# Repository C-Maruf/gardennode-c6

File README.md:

# GardenNode-C6

A solar-powered sensor node for gardens and greenhouses. It measures soil moisture, soil temperature, air temperature and humidity, then reports everything to Home Assistant over Wi-Fi. It can also switch a 12/24 V irrigation valve or pump.

**Status:** design complete (rev A). It hasn't been fabricated, so treat it as untested hardware.

## What it does

- Runs off a single 18650 cell, charged from a small 5–9 V solar panel or USB-C
- Wakes up every 10 minutes, takes readings, sends them, and goes back to sleep
- Two capacitive soil-moisture probes, one DS18B20 soil temperature probe, and a Qwiic port for an air sensor (SHT4x, SCD4x, etc.)
- Low-side valve driver for 5–24 V solenoids, with a 30-minute safety cut-off in firmware
- Reports battery and solar voltage so you can tell whether the panel is keeping up
- Fits in a 3D-printed, gasketed enclosure with cable glands

## Repo layout

```
hw/          KiCad schematic (+ PDF)
pcb/         KiCad board, DRC report, render
fab/         Gerbers, drill files, BOM, pick-and-place, assembly drawing
enclosure/   OpenSCAD source, STL and 3MF files
firmware/    ESPHome config
tools/       Python scripts that generate and check the design
```

## Hardware

**MCU:** ESP32-C6-WROOM-1. I picked it because it has Wi-Fi 6, Bluetooth LE and an 802.15.4 radio (Zigbee/Thread) in one FCC-certified module. It also has native USB, so the board doesn't need a USB-serial chip.

**Power:**
- **Charging:** USB-C and the solar input each go through a Schottky diode into a TI BQ24074 charger.
- **Solar handling:** the charger runs in USB500 mode, so its input-voltage regulation backs the current off when the panel sags. That's a cheap stand-in for proper MPPT.
- **Charge current:** set to about 0.6 A.
- **Temperature cut-off:** an NTC next to the cell stops charging below 0 °C or above 50 °C.
- **3.3 V rail:** a TLV75733 LDO, chosen for its 25 µA quiescent current.
- **Backwards cell:** a P-channel MOSFET between the cell and the charger blocks it if the cell is inserted the wrong way round.

**Sensors:**
- **Sensor rail:** the probes are powered from a switched 3.3 V rail (P-FET on GPIO4), so they draw nothing while the node sleeps.
- **Soil probes:** each input has a 1 k / 10 nF RC filter in front of the ADC.
- **1-Wire:** the bus has a 4.7 k pull-up.

**Valve output:**
- **Switch:** a DMN3404L low-side MOSFET.
- **Protection:** a flyback diode across the valve, plus a TVS diode on the supply input.

| GPIO | Use | GPIO | Use |
|---|---|---|---|
| 0, 1 | Soil probes (ADC) | 9 | BOOT button |
| 2 | Battery voltage ÷2 | 10 | Valve |
| 3 | Solar voltage ÷4 | 11 | Status LED (active low) |
| 4 | Sensor power (low = on) | 12, 13 | USB D−/D+ |
| 5 | 1-Wire | 16, 17 | UART on J8 |
| 6, 7 | I²C SDA/SCL | 18, 19 | Charge / power-good status |
| 8 | Strapping pin, pulled up | 20–23 | Spare, on J9 |

## PCB

- 100 × 82 mm, 2 layers, 1.6 mm FR-4, 1 oz copper
- 0.2 mm minimum track/space, 0.3 mm vias, which any standard fab can build
- Power traces widened to 0.4–1.0 mm, necked down only at fine-pitch pins
- Ground pour on both sides with stitching vias
- Copper keepout on both layers under the module antenna
- No vias in component pads, except the thermal vias under the charger and the module
- All parts on the top side; every part in the BOM is stocked at Digi-Key and Mouser

DRC is clean, with no unconnected nets and no clearance errors. The few items left in `pcb/drc.rpt` are expected:
- **USB-C peg spacing:** the manufacturer's land pattern puts its alignment pegs slightly closer to the pads than my rule allows.
- **Thermal spokes:** a few single-spoke thermal reliefs.
- **Edge silkscreen:** two marks clipped at the board edge.

## Enclosure

The enclosure source is OpenSCAD, so all the dimensions are parameters at the top of the file.

**Print settings:** ASA (or PETG), 0.2 mm layers, 4 walls. The USB-C plug is printed in TPU.

**Hardware:**
- 4× M3 screws for the board
- 4× M3×12 screws for the lid
- 3× PG7 cable glands
- 2 mm silicone cord in the lid groove as a gasket
- An adhesive ePTFE vent over the small hole so it doesn't fog up inside

**Fit and mounting:** the board sits close to the USB wall so a normal USB-C cable reaches the port. Mount the box glands-down.

## Firmware

The firmware is ESPHome, in `firmware/gardennode-c6.yaml`.

1. Copy `secrets.example.yaml` to `secrets.yaml` and fill in your Wi-Fi details and an API key.
2. Build it from ESPHome Builder in Home Assistant, or run `esphome run gardennode-c6.yaml`.
3. Flash it over USB-C. If the board doesn't show up, hold BOOT and tap RESET.

**Day-to-day behaviour:**
- **Staying awake:** turn on "Stay awake" in Home Assistant when you want to update or calibrate the node. The node also stays awake while the valve is open.
- **Probe calibration:** read the raw voltage dry and in water, then set `soil_dry_v` and `soil_wet_v` to match.

## If you build one

Bring it up in this order:

1. Power it from a current-limited 5 V supply with no battery fitted. VSYS should read about 4.4 V and the 3.3 V rail 3.30 V.
2. Flash the firmware and compare the battery and solar readings against a multimeter.
3. Fit the cell and check that it charges.
4. Test a reversed cell once. The 3.3 V rail should stay at 0 V.
5. Connect a 6 V panel and check that it charges.
6. Run a 12 V valve from the valve output.
7. Measure the sleep current.

## Known limitations

- **Untested hardware:** not fabricated or tested yet.
- **No end-product FCC certification:** the module has its own modular approval, but the finished board doesn't.
- **USB charging margin:** the Schottky diode on USB costs about 0.35 V, so a weak USB supply will charge slowly.
- **Low-battery cut-out:** the LDO drops out at about 3.5 V on the cell, so usable capacity ends a little early.

## How it was made

The schematic and board are KiCad 7 files, the enclosure is OpenSCAD and the firmware is ESPHome. The netlist lives in `tools/design.py`, and the schematic, board and BOM are all generated from it. Routing was done with a custom grid router in `tools/router.py`. I developed the design.

## License

## License

MIT. See [LICENSE](LICENSE).

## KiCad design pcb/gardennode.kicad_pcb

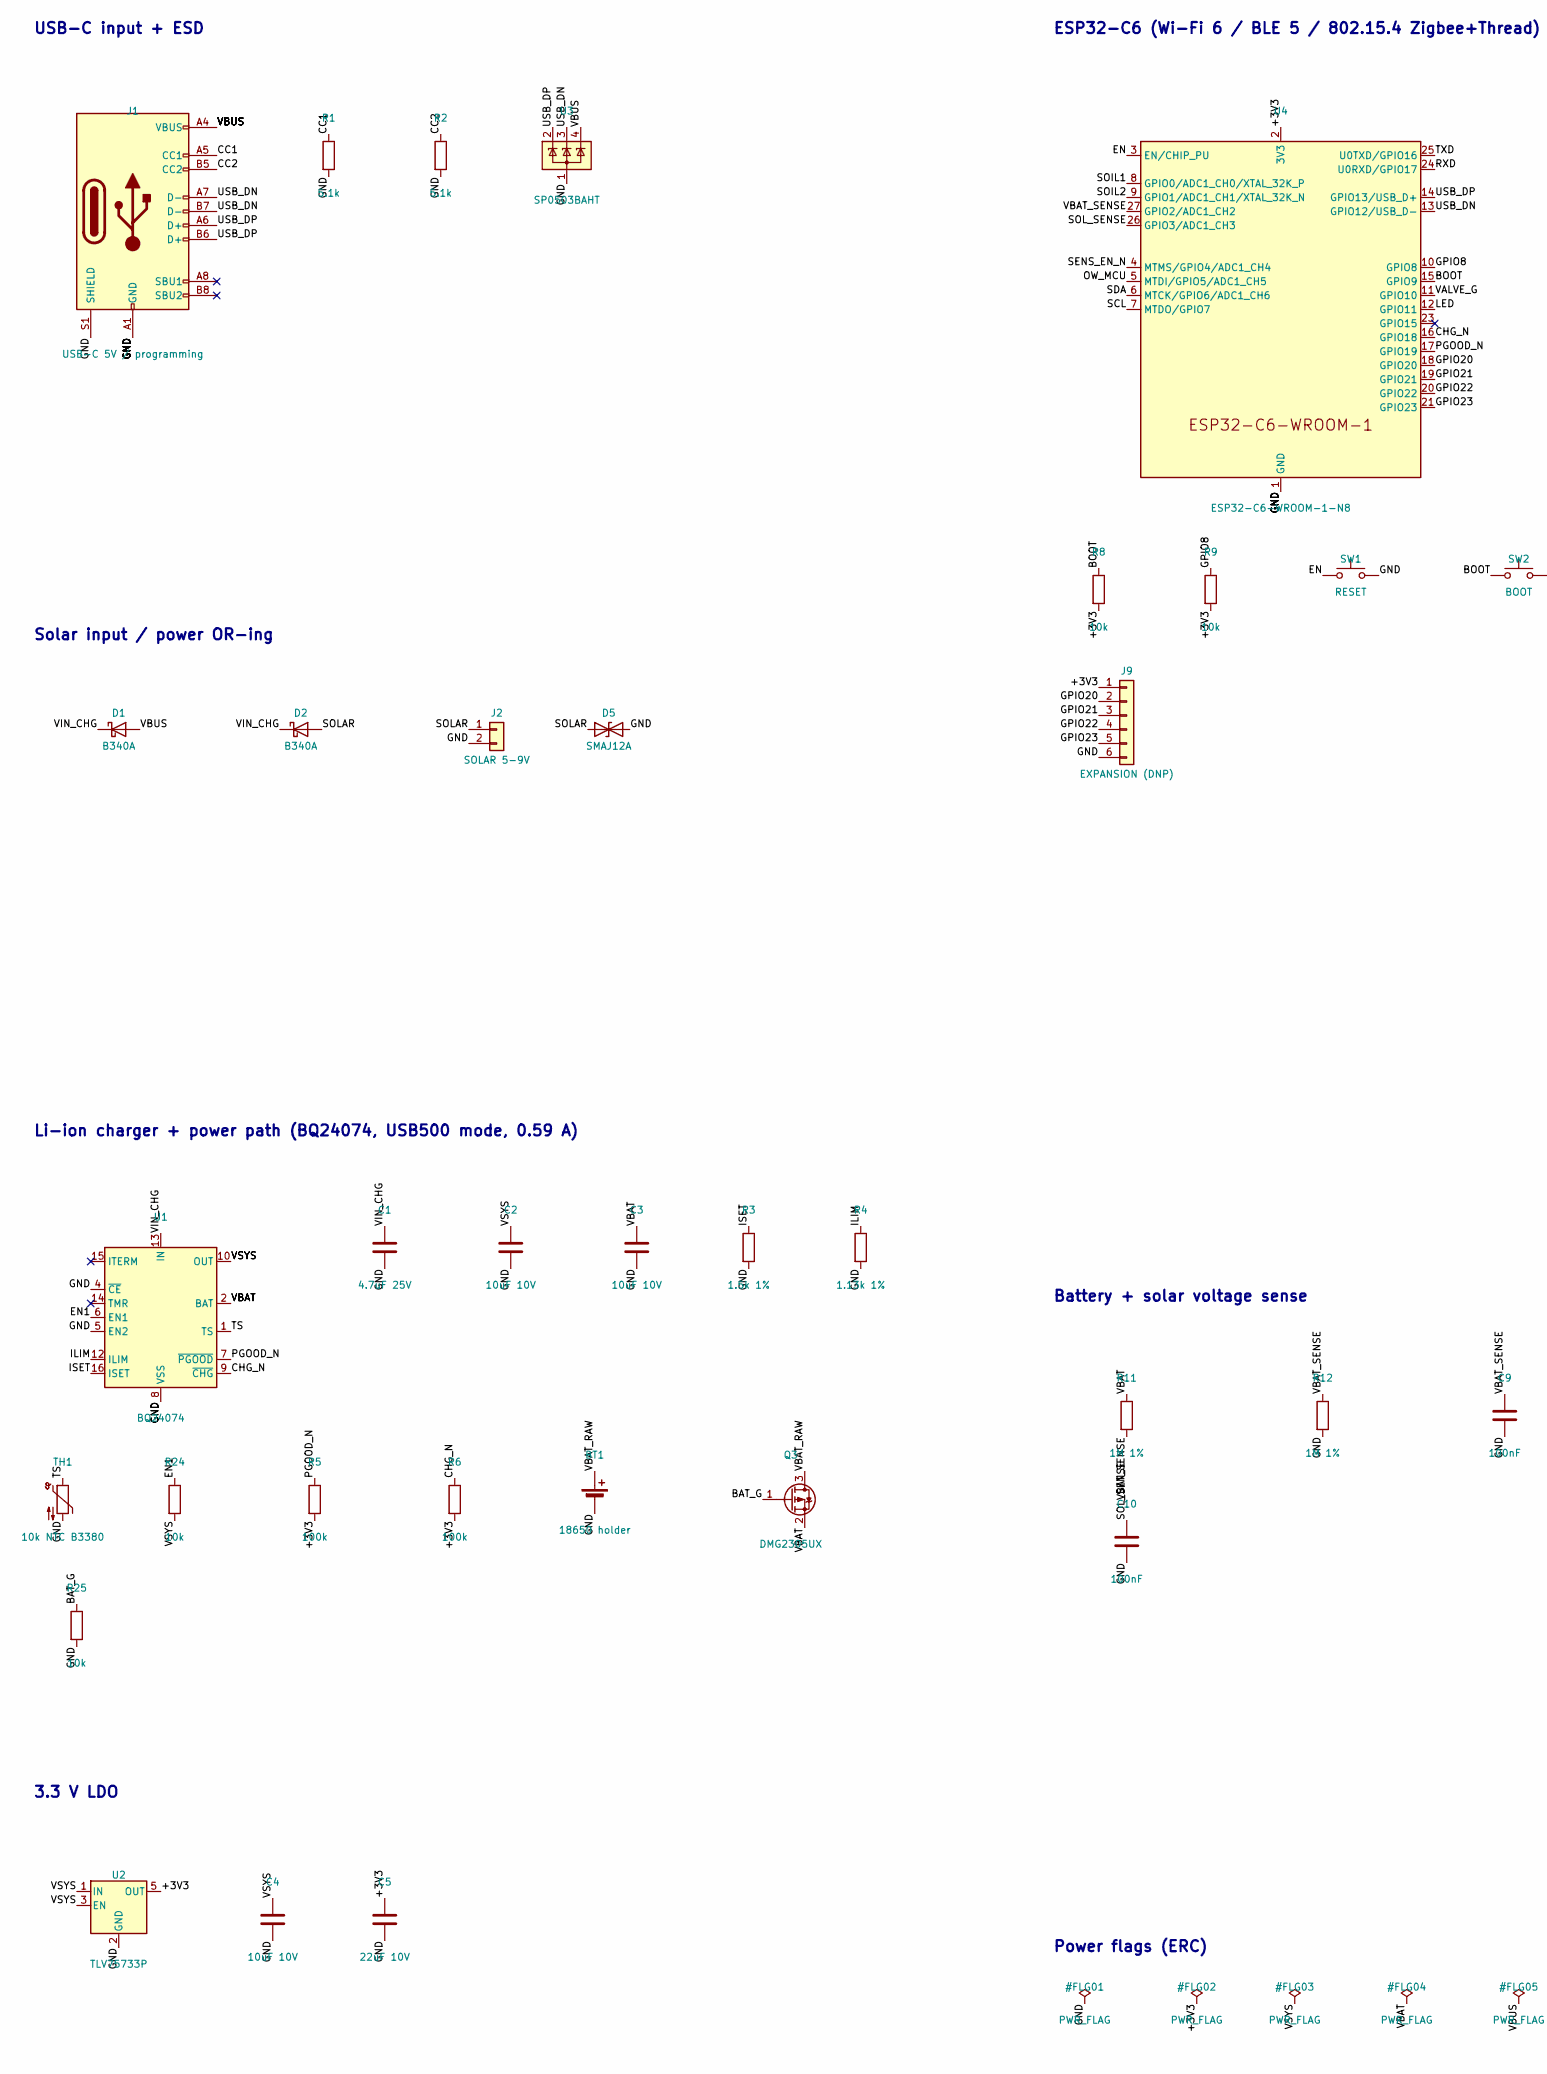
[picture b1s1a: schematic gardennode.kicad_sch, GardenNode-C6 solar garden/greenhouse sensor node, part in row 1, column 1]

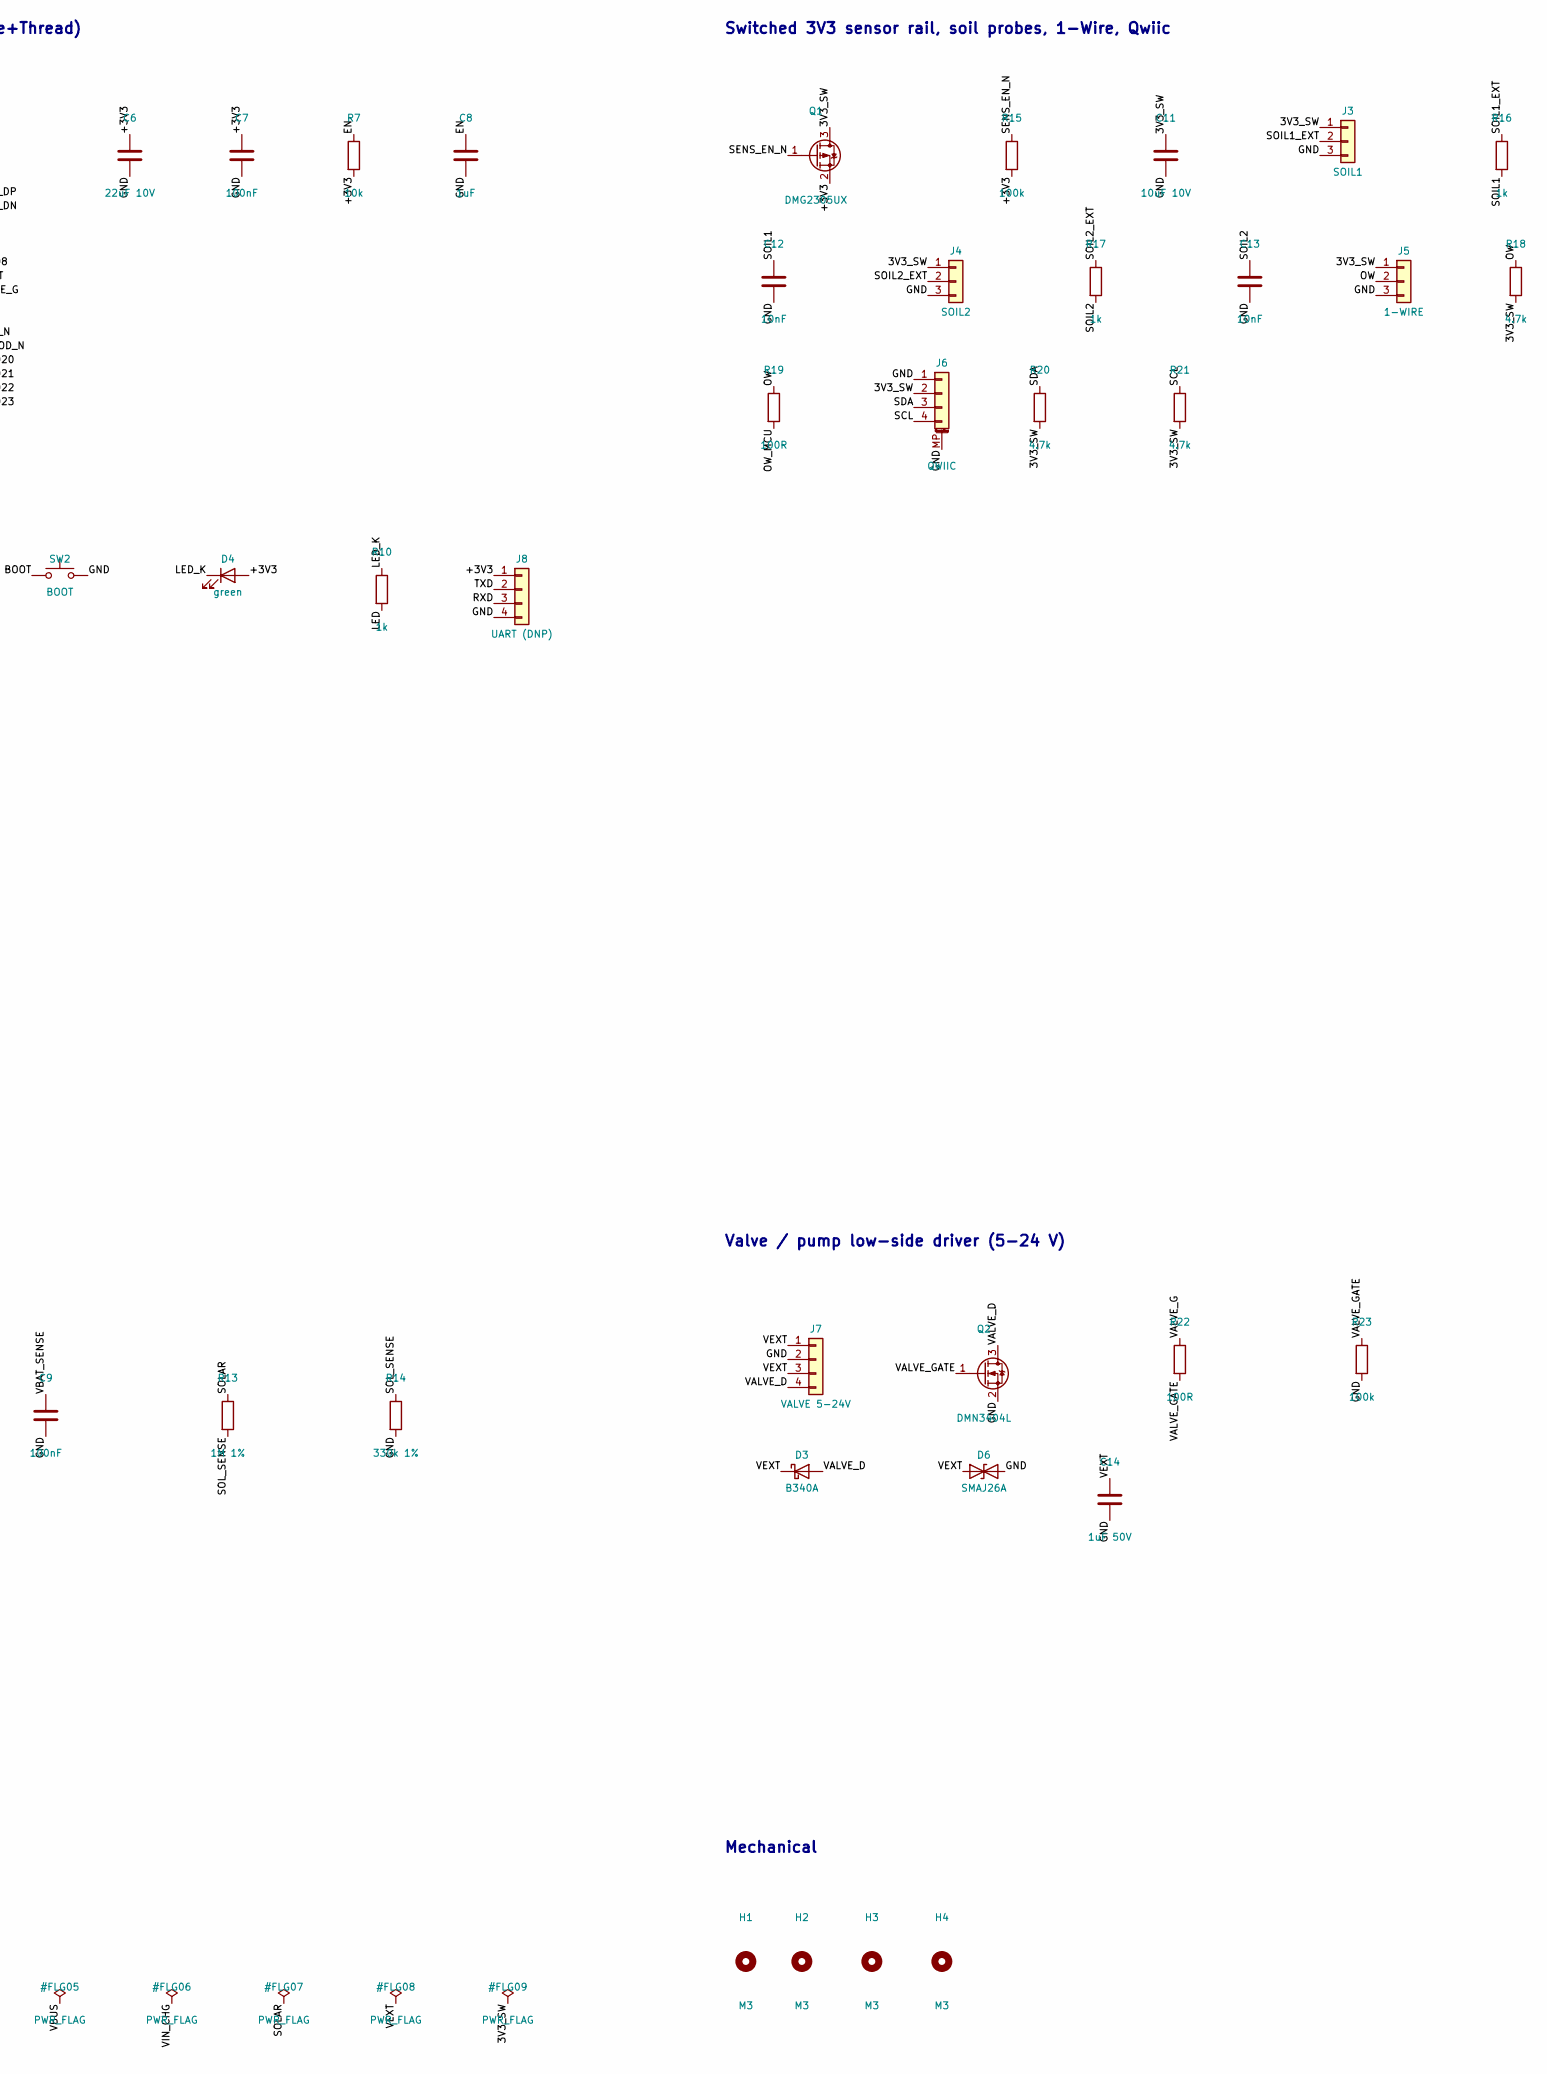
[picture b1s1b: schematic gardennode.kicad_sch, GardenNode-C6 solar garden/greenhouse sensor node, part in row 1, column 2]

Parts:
BT1: 18650 holder; BatteryHolder_Keystone_1042_1x18650; MPN 1042
C1: 4.7uF 25V; C_0805_2012Metric; MPN CL21A475KAQNNNE
C2, C3, C4, C11: 10uF 10V; C_0805_2012Metric; MPN CL21A106KPFNNNE
C5, C6: 22uF 10V; C_0805_2012Metric; MPN CL21A226MPQNNNE
C7, C9, C10: 100nF; C_0603_1608Metric; MPN CL10B104KB8NNNC
C8: 1uF; C_0603_1608Metric; MPN CL10A105KB8NNNC
C12, C13: 10nF; C_0603_1608Metric; MPN CL10B103KB8NNNC
C14: 1uF 50V; C_0805_2012Metric; MPN CL21B105KBFNNNE
D1, D2, D3: B340A; D_SMA; MPN B340A-13-F
D4: green; LED_0603_1608Metric; MPN LTST-C191KGKT
D5: SMAJ12A; D_SMA; MPN SMAJ12A
D6: SMAJ26A; D_SMA; MPN SMAJ26A
H1, H2, H3, H4: M3; MountingHole_3.2mm_M3
J1: USB-C 5V / programming; USB_C_Receptacle_GCT_USB4105-xx-A_16P_TopMnt_Horizontal; MPN USB4105-GF-A
J2: SOLAR 5-9V; TerminalBlock_Phoenix_PT-1,5-2-3.5-H_1x02_P3.50mm_Horizontal; MPN 1984617
J3: SOIL1; JST_PH_B3B-PH-K_1x03_P2.00mm_Vertical; MPN B3B-PH-K-S(LF)(SN)
J4: SOIL2; JST_PH_B3B-PH-K_1x03_P2.00mm_Vertical; MPN B3B-PH-K-S(LF)(SN)
J5: 1-WIRE; JST_PH_B3B-PH-K_1x03_P2.00mm_Vertical; MPN B3B-PH-K-S(LF)(SN)
J6: QWIIC; JST_SH_SM04B-SRSS-TB_1x04-1MP_P1.00mm_Horizontal; MPN SM04B-SRSS-TB(LF)(SN)
J7: VALVE 5-24V; TerminalBlock_Phoenix_PT-1,5-4-3.5-H_1x04_P3.50mm_Horizontal; MPN 1984633
J8: UART (DNP); PinHeader_1x04_P2.54mm_Vertical; MPN DNP
J9: EXPANSION (DNP); PinHeader_1x06_P2.54mm_Vertical; MPN DNP
Q1, Q3: DMG2305UX; SOT-23; MPN DMG2305UX-7
Q2: DMN3404L; SOT-23; MPN DMN3404L-7
R1, R2: 5.1k; R_0603_1608Metric; MPN RC0603FR-075K1L
R3: 1.5k 1%; R_0603_1608Metric; MPN RC0603FR-071K5L
R4: 1.13k 1%; R_0603_1608Metric; MPN RC0603FR-071K13L
R5, R6, R15, R23: 100k; R_0603_1608Metric; MPN RC0603FR-07100KL
R7, R8, R9, R24, R25: 10k; R_0603_1608Metric; MPN RC0603FR-0710KL
R10, R16, R17: 1k; R_0603_1608Metric; MPN RC0603FR-071KL
R11, R12, R13: 1M 1%; R_0603_1608Metric; MPN RC0603FR-071ML
R14: 330k 1%; R_0603_1608Metric; MPN RC0603FR-07330KL
R18, R20, R21: 4.7k; R_0603_1608Metric; MPN RC0603FR-074K7L
R19, R22: 100R; R_0603_1608Metric; MPN RC0603FR-07100RL
SW1: RESET; SW_Push_1P1T_NO_CK_KMR2; MPN KMR221GLFS
SW2: BOOT; SW_Push_1P1T_NO_CK_KMR2; MPN KMR221GLFS
TH1: 10k NTC B3380; R_0603_1608Metric; MPN NCP18XH103F03RB
U1: BQ24074; VQFN-16-1EP_3x3mm_P0.5mm_EP1.6x1.6mm; MPN BQ24074RGTR
U2: TLV75733P; SOT-23-5; MPN TLV75733PDBVR
U3: SP0503BAHT; SOT-143; MPN SP0503BAHTG
U4: ESP32-C6-WROOM-1-N8; ESP32-C6-WROOM-1; MPN ESP32-C6-WROOM-1-N8

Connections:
3V3_SW: C11.1, J3.1, J4.1, J5.1, J6.2, Q1.3 (D), R18.2, R20.2, R21.2
+3V3: C5.1, C6.1, C7.1, D4.2 (A), J8.1, J9.1, Q1.2 (S), R5.2, R6.2, R7.2, R8.2, R9.2, R15.2, U2.5 (OUT), U4.2 (3V3)
BAT_G: Q3.1 (G), R25.1
BOOT: R8.1, SW2.1, U4.15 (GPIO9)
CC1: J1.A5 (CC1), R1.1
CC2: J1.B5 (CC2), R2.1
CHG_N: R6.1, U1.9 (~CHG), U4.16 (GPIO18)
EN: C8.1, R7.1, SW1.1, U4.3 (EN/CHIP_PU)
EN1: R24.1, U1.6 (EN1)
GND: BT1.2 (-), C1.2, C2.2, C3.2, C4.2, C5.2, C6.2, C7.2, C8.2, C9.2, C10.2, C11.2, C12.2, C13.2, C14.2, D5.2 (A2), D6.2 (A2), J1.A1 (GND), J1.A12 (GND), J1.B1 (GND), J1.B12 (GND), J1.S1 (SHIELD), J2.2, J3.3, J4.3, J5.3, J6.1, J6.MP (MountPin), J7.2, J8.4, J9.6, Q2.2 (S), R1.2, R2.2, R3.2, R4.2, R12.2, R14.2, R23.2, R25.2, SW1.2, SW2.2, TH1.2, U1.4 (~CE), U1.5 (EN2), U1.8 (VSS), U1.17 (VSS), U2.2 (GND), U3.1 (A), U4.1 (GND), U4.28 (GND), U4.29 (GND)
GPIO8: R9.1, U4.10 (GPIO8)
GPIO20: J9.2, U4.18 (GPIO20)
GPIO21: J9.3, U4.19 (GPIO21)
GPIO22: J9.4, U4.20 (GPIO22)
GPIO23: J9.5, U4.21 (GPIO23)
ILIM: R4.1, U1.12 (ILIM)
ISET: R3.1, U1.16 (ISET)
LED: R10.2, U4.12 (GPIO11)
LED_K: D4.1 (K), R10.1
OW: J5.2, R18.1, R19.1
OW_MCU: R19.2, U4.5 (MTDI/GPIO5/ADC1_CH5)
PGOOD_N: R5.1, U1.7 (~PGOOD), U4.17 (GPIO19)
RXD: J8.3, U4.24 (U0RXD/GPIO17)
SCL: J6.4, R21.1, U4.7 (MTDO/GPIO7)
SDA: J6.3, R20.1, U4.6 (MTCK/GPIO6/ADC1_CH6)
SENS_EN_N: Q1.1 (G), R15.1, U4.4 (MTMS/GPIO4/ADC1_CH4)
SOIL1: C12.1, R16.2, U4.8 (GPIO0/ADC1_CH0/XTAL_32K_P)
SOIL1_EXT: J3.2, R16.1
SOIL2: C13.1, R17.2, U4.9 (GPIO1/ADC1_CH1/XTAL_32K_N)
SOIL2_EXT: J4.2, R17.1
SOLAR: D2.2 (A), D5.1 (A1), J2.1, R13.1
SOL_SENSE: C10.1, R13.2, R14.1, U4.26 (GPIO3/ADC1_CH3)
TS: TH1.1, U1.1 (TS)
TXD: J8.2, U4.25 (U0TXD/GPIO16)
USB_DN: J1.A7 (D-), J1.B7 (D-), U3.3 (K), U4.13 (GPIO12/USB_D-)
USB_DP: J1.A6 (D+), J1.B6 (D+), U3.2 (K), U4.14 (GPIO13/USB_D+)
VALVE_D: D3.2 (A), J7.4, Q2.3 (D)
VALVE_G: R22.1, U4.11 (GPIO10)
VALVE_GATE: Q2.1 (G), R22.2, R23.1
VBAT: C3.1, Q3.2 (S), R11.1, U1.2 (BAT), U1.3 (BAT)
VBAT_RAW: BT1.1 (+), Q3.3 (D)
VBAT_SENSE: C9.1, R11.2, R12.1, U4.27 (GPIO2/ADC1_CH2)
VBUS: D1.2 (A), J1.A4 (VBUS), J1.A9 (VBUS), J1.B4 (VBUS), J1.B9 (VBUS), U3.4 (K)
VEXT: C14.1, D3.1 (K), D6.1 (A1), J7.1, J7.3
VIN_CHG: C1.1, D1.1 (K), D2.1 (K), U1.13 (IN)
VSYS: C2.1, C4.1, R24.2, U1.10 (OUT), U1.11 (OUT), U2.1 (IN), U2.3 (EN)

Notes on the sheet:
USB-C input + ESD
Solar input / power OR-ing
Li-ion charger + power path (BQ24074, USB500 mode, 0.59 A)
3.3 V LDO
ESP32-C6 (Wi-Fi 6 / BLE 5 / 802.15.4 Zigbee+Thread)
Battery + solar voltage sense
Switched 3V3 sensor rail, soil probes, 1-Wire, Qwiic
Valve / pump low-side driver (5-24 V)
Mechanical
Power flags (ERC)

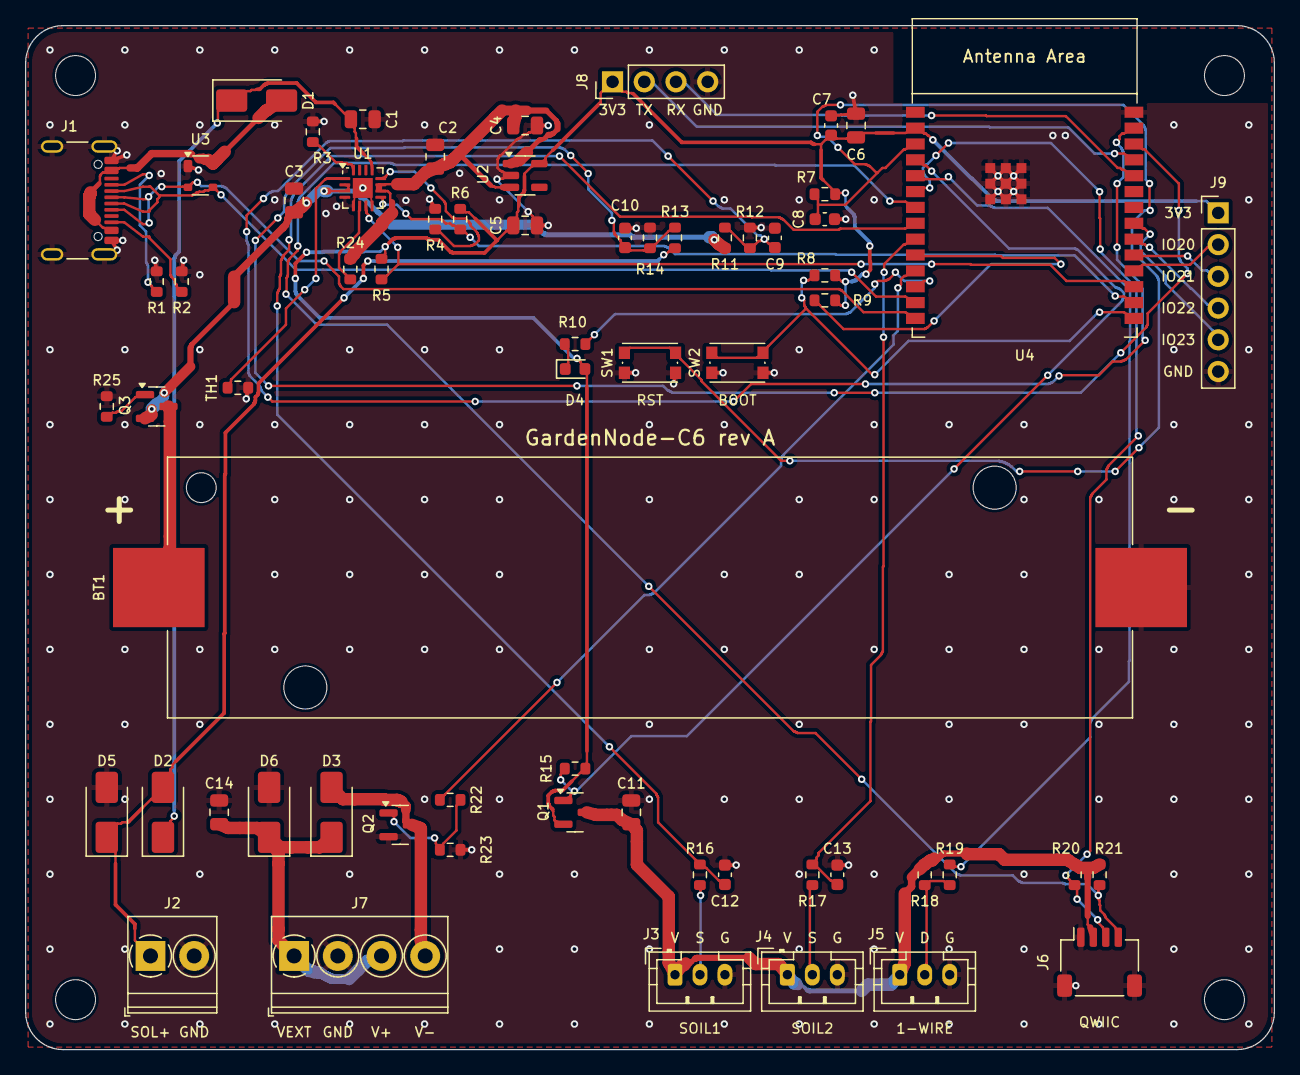
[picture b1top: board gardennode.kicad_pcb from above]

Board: 2 copper layers, 100.0 x 82.0 mm, 69 parts (0 on the bottom side), 46 nets.

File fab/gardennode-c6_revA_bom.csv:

Item,Qty,References,Value,Footprint,Manufacturer,MPN,US distributors,Approved alternate,Populate
1,1,BT1,18650 holder,BatteryHolder_Keystone_1042_1x18650,Keystone,1042,"DK, MO",1042P (polarized),Yes
2,1,C1,4.7uF 25V,C_0805_2012Metric,Samsung Electro-Mechanics,CL21A475KAQNNNE,"DK, MO","any AEC/X7R-equivalent 0603/0805 part, same value/voltage/tolerance",Yes
3,4,C2 C3 C4 C11,10uF 10V,C_0805_2012Metric,Samsung Electro-Mechanics,CL21A106KPFNNNE,"DK, MO","any AEC/X7R-equivalent 0603/0805 part, same value/voltage/tolerance",Yes
4,2,C5 C6,22uF 10V,C_0805_2012Metric,Samsung Electro-Mechanics,CL21A226MPQNNNE,"DK, MO","any AEC/X7R-equivalent 0603/0805 part, same value/voltage/tolerance",Yes
5,3,C7 C9 C10,100nF,C_0603_1608Metric,Samsung Electro-Mechanics,CL10B104KB8NNNC,"DK, MO","any AEC/X7R-equivalent 0603/0805 part, same value/voltage/tolerance",Yes
6,1,C8,1uF,C_0603_1608Metric,Samsung Electro-Mechanics,CL10A105KB8NNNC,"DK, MO","any AEC/X7R-equivalent 0603/0805 part, same value/voltage/tolerance",Yes
7,2,C12 C13,10nF,C_0603_1608Metric,Samsung Electro-Mechanics,CL10B103KB8NNNC,"DK, MO","any AEC/X7R-equivalent 0603/0805 part, same value/voltage/tolerance",Yes
8,1,C14,1uF 50V,C_0805_2012Metric,Samsung Electro-Mechanics,CL21B105KBFNNNE,"DK, MO","any AEC/X7R-equivalent 0603/0805 part, same value/voltage/tolerance",Yes
9,3,D1 D2 D3,B340A,D_SMA,Diodes Inc,B340A-13-F,"DK, MO",B340A-E3/61T (Vishay),Yes
10,1,D4,green,LED_0603_1608Metric,Lite-On,LTST-C191KGKT,"DK, MO",,Yes
11,1,D5,SMAJ12A,D_SMA,Littelfuse,SMAJ12A,"DK, MO",SMAJ12A-13-F (Diodes),Yes
12,1,D6,SMAJ26A,D_SMA,Littelfuse,SMAJ26A,"DK, MO",SMAJ26A-13-F (Diodes),Yes
13,1,J1,USB-C 5V / programming,USB_C_Receptacle_GCT_USB4105-xx-A_16P_TopMnt_Horizontal,GCT,USB4105-GF-A,"DK, MO",USB4105-GF-A-060,Yes
14,1,J2,SOLAR 5-9V,"TerminalBlock_Phoenix_PT-1,5-2-3.5-H_1x02_P3.50mm_Horizontal",Phoenix Contact,1984617,"DK, MO",,Yes
15,1,J3,SOIL1,JST_PH_B3B-PH-K_1x03_P2.00mm_Vertical,JST,B3B-PH-K-S(LF)(SN),"DK, MO",,Yes
16,1,J4,SOIL2,JST_PH_B3B-PH-K_1x03_P2.00mm_Vertical,JST,B3B-PH-K-S(LF)(SN),"DK, MO",,Yes
17,1,J5,1-WIRE,JST_PH_B3B-PH-K_1x03_P2.00mm_Vertical,JST,B3B-PH-K-S(LF)(SN),"DK, MO",,Yes
18,1,J6,QWIIC,JST_SH_SM04B-SRSS-TB_1x04-1MP_P1.00mm_Horizontal,JST,SM04B-SRSS-TB(LF)(SN),"DK, MO",,Yes
19,1,J7,VALVE 5-24V,"TerminalBlock_Phoenix_PT-1,5-4-3.5-H_1x04_P3.50mm_Horizontal",Phoenix Contact,1984633,"DK, MO",,Yes
20,1,J8,UART (DNP),PinHeader_1x04_P2.54mm_Vertical,-,"PRT-00116 (SparkFun) or any 0.1"" header",-,,DNP
21,1,J9,EXPANSION (DNP),PinHeader_1x06_P2.54mm_Vertical,-,"PRT-00116 (SparkFun) or any 0.1"" header",-,,DNP
22,2,Q1 Q3,DMG2305UX,SOT-23,Diodes Inc,DMG2305UX-7,"DK, MO",DMG2307L-7,Yes
23,1,Q2,DMN3404L,SOT-23,Diodes Inc,DMN3404L-7,"DK, MO",DMG3404L-7,Yes
24,2,R1 R2,5.1k,R_0603_1608Metric,Yageo,RC0603FR-075K1L,"DK, MO","any AEC/X7R-equivalent 0603/0805 part, same value/voltage/tolerance",Yes
25,1,R3,1.5k 1%,R_0603_1608Metric,Yageo,RC0603FR-071K5L,"DK, MO","any AEC/X7R-equivalent 0603/0805 part, same value/voltage/tolerance",Yes
26,1,R4,1.13k 1%,R_0603_1608Metric,Yageo,RC0603FR-071K13L,"DK, MO","any AEC/X7R-equivalent 0603/0805 part, same value/voltage/tolerance",Yes
27,4,R5 R6 R15 R23,100k,R_0603_1608Metric,Yageo,RC0603FR-07100KL,"DK, MO","any AEC/X7R-equivalent 0603/0805 part, same value/voltage/tolerance",Yes
28,5,R7 R8 R9 R24 R25,10k,R_0603_1608Metric,Yageo,RC0603FR-0710KL,"DK, MO","any AEC/X7R-equivalent 0603/0805 part, same value/voltage/tolerance",Yes
29,3,R10 R16 R17,1k,R_0603_1608Metric,Yageo,RC0603FR-071KL,"DK, MO","any AEC/X7R-equivalent 0603/0805 part, same value/voltage/tolerance",Yes
30,3,R11 R12 R13,1M 1%,R_0603_1608Metric,Yageo,RC0603FR-071ML,"DK, MO","any AEC/X7R-equivalent 0603/0805 part, same value/voltage/tolerance",Yes
31,1,R14,330k 1%,R_0603_1608Metric,Yageo,RC0603FR-07330KL,"DK, MO","any AEC/X7R-equivalent 0603/0805 part, same value/voltage/tolerance",Yes
32,3,R18 R20 R21,4.7k,R_0603_1608Metric,Yageo,RC0603FR-074K7L,"DK, MO","any AEC/X7R-equivalent 0603/0805 part, same value/voltage/tolerance",Yes
33,2,R19 R22,100R,R_0603_1608Metric,Yageo,RC0603FR-07100RL,"DK, MO","any AEC/X7R-equivalent 0603/0805 part, same value/voltage/tolerance",Yes
34,1,SW1,RESET,SW_Push_1P1T_NO_CK_KMR2,C&K,KMR221GLFS,"DK, MO",,Yes
35,1,SW2,BOOT,SW_Push_1P1T_NO_CK_KMR2,C&K,KMR221GLFS,"DK, MO",,Yes
36,1,TH1,10k NTC B3380,R_0603_1608Metric,Murata,NCP18XH103F03RB,"DK, MO",NTCG163JF103FT1 (TDK),Yes
37,1,U1,BQ24074,VQFN-16-1EP_3x3mm_P0.5mm_EP1.6x1.6mm,Texas Instruments,BQ24074RGTR,"DK, MO, TI.com",BQ24074RGTT (small reel),Yes
38,1,U2,TLV75733P,SOT-23-5,Texas Instruments,TLV75733PDBVR,"DK, MO, TI.com","TLV75733PDYDR, TLV75533PDBVR (0.5 A)",Yes
39,1,U3,SP0503BAHT,SOT-143,Littelfuse,SP0503BAHTG,"DK, MO",,Yes
40,1,U4,ESP32-C6-WROOM-1-N8,ESP32-C6-WROOM-1,Espressif,ESP32-C6-WROOM-1-N8,"DK, MO",ESP32-C6-WROOM-1-N4 (4 MB flash),Yes

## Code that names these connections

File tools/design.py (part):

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P(R('R2', '5.1k', 'CC2', 'GND', 'RC0603FR-075K1L', grp='usb'))
P(dict(ref='U3', lib=SYM+'Power_Protection.kicad_sym', sym='SP0503BAHT', fp='Package_TO_SOT_SMD:SOT-143',
       value='SP0503BAHT', mfr='Littelfuse', mpn='SP0503BAHTG',
       pins={'1': 'GND', '2': 'USB_DP', '3': 'USB_DN', '4': 'VBUS'}, grp='usb'))

# ---------------- Power input OR-ing ----------------
P(dict(ref='D1', lib=SYM+'Device.kicad_sym', sym='D_Schottky', fp='Diode_SMD:D_SMA', value='B340A',
       mfr='Diodes Inc', mpn='B340A-13-F', pins={'1': 'VIN_CHG', '2': 'VBUS'}, grp='pwr'))
P(dict(ref='D2', lib=SYM+'Device.kicad_sym', sym='D_Schottky', fp='Diode_SMD:D_SMA', value='B340A',
       mfr='Diodes Inc', mpn='B340A-13-F', pins={'1': 'VIN_CHG', '2': 'SOLAR'}, grp='pwr'))
P(dict(ref='J2', lib=SYM+'Connector_Generic.kicad_sym', sym='Conn_01x02',
       fp='TerminalBlock_Phoenix:TerminalBlock_Phoenix_PT-1,5-2-3.5-H_1x02_P3.50mm_Horizontal',
       value='SOLAR 5-9V', mfr='Phoenix Contact', mpn='1984617', pins={'1': 'SOLAR', '2': 'GND'}, grp='pwr'))
P(dict(ref='D5', lib=SYM+'Device.kicad_sym', sym='D_TVS', fp='Diode_SMD:D_SMA', value='SMAJ12A',
       mfr='Littelfuse', mpn='SMAJ12A', pins={'1': 'SOLAR', '2': 'GND'}, grp='pwr'))

# ---------------- Charger BQ24074 ----------------
P(dict(ref='U1', lib=SYM+'Battery_Management.kicad_sym', sym='BQ24074RGT',
       fp='Package_DFN_QFN:VQFN-16-1EP_3x3mm_P0.5mm_EP1.6x1.6mm', value='BQ24074', mfr='Texas Instruments', mpn='BQ24074RGTR',
       pins={'1': 'TS', '2': 'VBAT', '3': 'VBAT', '4': 'GND', '5': 'GND', '6': 'EN1', '7': 'PGOOD_N', '8': 'GND',
             '9': 'CHG_N', '10': 'VSYS', '11': 'VSYS', '12': 'ILIM', '13': 'VIN_CHG', '14': NC, '15': NC, '16': 'ISET', '17': 'GND'}, grp='chg'))
P(C('C1', '4.7uF 25V', 'VIN_CHG', 'GND', 'CL21A475KAQNNNE', fp='Capacitor_SMD:C_0805_2012Metric', grp='chg'))
P(C('C2', '10uF 10V', 'VSYS', 'GND', 'CL21A106KPFNNNE', fp='Capacitor_SMD:C_0805_2012Metric', grp='chg'))
P(C('C3', '10uF 10V', 'VBAT', 'GND', 'CL21A106KPFNNNE', fp='Capacitor_SMD:C_0805_2012Metric', grp='chg'))
P(R('R3', '1.5k 1%', 'ISET', 'GND', 'RC0603FR-071K5L', grp='chg'))      # ICHG = 890/1500 = 0.59 A
P(R('R4', '1.13k 1%', 'ILIM', 'GND', 'RC0603FR-071K13L', grp='chg'))    # only used if EN2=1/EN1=0
P(dict(ref='TH1', lib=SYM+'Device.kicad_sym', sym='Thermistor_NTC', fp='Resistor_SMD:R_0603_1608Metric',
       value='10k NTC B3380', mfr='Murata', mpn='NCP18XH103F03RB', pins={'1': 'TS', '2': 'GND'}, grp='chg'))
P(R('R24', '10k', 'EN1', 'VSYS', 'RC0603FR-0710KL', grp='chg'))   # EN1=1, EN2=0 -> USB500 (VIN-DPM active)
P(R('R5', '100k', 'PGOOD_N', '+3V3', 'RC0603FR-07100KL', grp='chg'))
P(R('R6', '100k', 'CHG_N', '+3V3', 'RC0603FR-07100KL', grp='chg'))
P(dict(ref='BT1', lib=SYM+'Device.kicad_sym', sym='Battery_Cell', fp='Battery:BatteryHolder_Keystone_1042_1x18650',
       value='18650 holder', mfr='Keystone', mpn='1042', pins={'1': 'VBAT_RAW', '2': 'GND'}, grp='chg'))
# reverse-battery protection: P-FET, drain to cell +, source to VBAT, gate to GND.
# Correct cell: body diode conducts, Vgs = -Vbat turns the channel on (works both ways, so charging still flows).
# Reversed cell: body diode blocked and gate off -> nothing downstream sees negative voltage.
P(dict(ref='Q3', lib=SYM+'Device.kicad_sym', sym='Q_PMOS_GSD', fp='Package_TO_SOT_SMD:SOT-23', value='DMG2305UX',
       mfr='Diodes Inc', mpn='DMG2305UX-7', pins={'1': 'BAT_G', '2': 'VBAT', '3': 'VBAT_RAW'}, grp='chg'))
P(R('R25', '10k', 'BAT_G', 'GND', 'RC0603FR-0710KL', grp='chg'))

# ---------------- 3.3 V LDO ----------------
P(dict(ref='U2', lib=SYM+'Regulator_Linear.kicad_sym', sym='TLV75733PDBV', fp='Package_TO_SOT_SMD:SOT-23-5',
       value='TLV75733P', mfr='Texas Instruments', mpn='TLV75733PDBVR',
       pins={'1': 'VSYS', '2': 'GND', '3': 'VSYS', '4': NC, '5': '+3V3'}, grp='ldo'))
P(C('C4', '10uF 10V', 'VSYS', 'GND', 'CL21A106KPFNNNE', fp='Capacitor_SMD:C_0805_2012Metric', grp='ldo'))
P(C('C5', '22uF 10V', '+3V3', 'GND', 'CL21A226MPQNNNE', fp='Capacitor_SMD:C_0805_2012Metric', grp='ldo'))

# ---------------- ESP32-C6 ----------------
P(dict(ref='U4', lib=ESPSYM, sym='ESP32-C6-WROOM-1', fp='Espressif:ESP32-C6-WROOM-1',
       value='ESP32-C6-WROOM-1-N8', mfr='Espressif', mpn='ESP32-C6-WROOM-1-N8',
       pins={'1': 'GND', '2': '+3V3', '3': 'EN', '4': 'SENS_EN_N', '5': 'OW_MCU', '6': 'SDA', '7': 'SCL',
             '8': 'SOIL1', '9': 'SOIL2', '10': 'GPIO8', '11': 'VALVE_G', '12': 'LED', '13': 'USB_DN', '14': 'USB_DP',
             '15': 'BOOT', '16': 'CHG_N', '17': 'PGOOD_N', '18': 'GPIO20', '19': 'GPIO21', '20': 'GPIO22', '21': 'GPIO23',
             '22': NC, '23': NC, '24': 'RXD', '25': 'TXD', '26': 'SOL_SENSE', '27': 'VBAT_SENSE', '28': 'GND', '29': 'GND'}, grp='mcu'))
P(C('C6', '22uF 10V', '+3V3', 'GND', 'CL21A226MPQNNNE', fp='Capacitor_SMD:C_0805_2012Metric', grp='mcu'))
P(C('C7', '100nF', '+3V3', 'GND', 'CL10B104KB8NNNC', grp='mcu'))
P(R('R7', '10k', 'EN', '+3V3', 'RC0603FR-0710KL', grp='mcu'))
P(C('C8', '1uF', 'EN', 'GND', 'CL10A105KB8NNNC', grp='mcu'))
P(R('R8', '10k', 'BOOT', '+3V3', 'RC0603FR-0710KL', grp='mcu'))
P(R('R9', '10k', 'GPIO8', '+3V3', 'RC0603FR-0710KL', grp='mcu'))
P(dict(ref='SW1', lib=SYM+'Switch.kicad_sym', sym='SW_Push', fp='Button_Switch_SMD:SW_Push_1P1T_NO_CK_KMR2',
       value='RESET', mfr='C&K', mpn='KMR221GLFS', pins={'1': 'EN', '2': 'GND'}, grp='mcu'))
P(dict(ref='SW2', lib=SYM+'Switch.kicad_sym', sym='SW_Push', fp='Button_Switch_SMD:SW_Push_1P1T_NO_CK_KMR2',
       value='BOOT', mfr='C&K', mpn='KMR221GLFS', pins={'1': 'BOOT', '2': 'GND'}, grp='mcu'))
P(dict(ref='D4', lib=SYM+'Device.kicad_sym', sym='LED', fp='LED_SMD:LED_0603_1608Metric', value='green',
       mfr='Lite-On', mpn='LTST-C191KGKT', pins={'1': 'LED_K', '2': '+3V3'}, grp='mcu'))
P(R('R10', '1k', 'LED_K', 'LED', 'RC0603FR-071KL', grp='mcu'))   # active-low LED, off at reset
P(dict(ref='J8', lib=SYM+'Connector_Generic.kicad_sym', sym='Conn_01x04', fp='Connector_PinHeader_2.54mm:PinHeader_1x04_P2.54mm_Vertical',
       value='UART (DNP)', mfr='Amphenol', mpn='DNP', pins={'1': '+3V3', '2': 'TXD', '3': 'RXD', '4': 'GND'}, grp='mcu'))
P(dict(ref='J9', lib=SYM+'Connector_Generic.kicad_sym', sym='Conn_01x06', fp='Connector_PinHeader_2.54mm:PinHeader_1x06_P2.54mm_Vertical',
       value='EXPANSION (DNP)', mfr='Amphenol', mpn='DNP', pins={'1': '+3V3', '2': 'GPIO20', '3': 'GPIO21', '4': 'GPIO22', '5': 'GPIO23', '6': 'GND'}, grp='mcu'))

# ---------------- Measurement ----------------
P(R('R11', '1M 1%', 'VBAT', 'VBAT_SENSE', 'RC0603FR-071ML', grp='meas'))
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
# ---------------- Switched sensor rail ----------------
P(dict(ref='Q1', lib=SYM+'Device.kicad_sym', sym='Q_PMOS_GSD', fp='Package_TO_SOT_SMD:SOT-23', value='DMG2305UX',
       mfr='Diodes Inc', mpn='DMG2305UX-7', pins={'1': 'SENS_EN_N', '2': '+3V3', '3': '3V3_SW'}, grp='sens'))
P(R('R15', '100k', 'SENS_EN_N', '+3V3', 'RC0603FR-07100KL', grp='sens'))
P(C('C11', '10uF 10V', '3V3_SW', 'GND', 'CL21A106KPFNNNE', fp='Capacitor_SMD:C_0805_2012Metric', grp='sens'))

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P(dict(ref='J7', lib=SYM+'Connector_Generic.kicad_sym', sym='Conn_01x04',
       fp='TerminalBlock_Phoenix:TerminalBlock_Phoenix_PT-1,5-4-3.5-H_1x04_P3.50mm_Horizontal',
       value='VALVE 5-24V', mfr='Phoenix Contact', mpn='1984633',
       pins={'1': 'VEXT', '2': 'GND', '3': 'VEXT', '4': 'VALVE_D'}, grp='valve'))
P(dict(ref='Q2', lib=SYM+'Device.kicad_sym', sym='Q_NMOS_GSD', fp='Package_TO_SOT_SMD:SOT-23', value='DMN3404L',
       mfr='Diodes Inc', mpn='DMN3404L-7', pins={'1': 'VALVE_GATE', '2': 'GND', '3': 'VALVE_D'}, grp='valve'))
P(R('R22', '100R', 'VALVE_G', 'VALVE_GATE', 'RC0603FR-07100RL', grp='valve'))
P(R('R23', '100k', 'VALVE_GATE', 'GND', 'RC0603FR-07100KL', grp='valve'))
P(dict(ref='D3', lib=SYM+'Device.kicad_sym', sym='D_Schottky', fp='Diode_SMD:D_SMA', value='B340A',
       mfr='Diodes Inc', mpn='B340A-13-F', pins={'1': 'VEXT', '2': 'VALVE_D'}, grp='valve'))
P(dict(ref='D6', lib=SYM+'Device.kicad_sym', sym='D_TVS', fp='Diode_SMD:D_SMA', value='SMAJ26A',
       mfr='Littelfuse', mpn='SMAJ26A', pins={'1': 'VEXT', '2': 'GND'}, grp='valve'))
P(C('C14', '1uF 50V', 'VEXT', 'GND', 'CL21B105KBFNNNE', fp='Capacitor_SMD:C_0805_2012Metric', grp='valve'))

# ---------------- Mechanical ----------------
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
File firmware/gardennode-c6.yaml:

# GardenNode-C6 rev A - ESPHome firmware
# Flash once over USB-C (ESPHome web flasher or `esphome run`), then updates go over the air.
# Wake every 10 min, measure, report to Home Assistant, deep-sleep (~25 uA board + probe leakage).
# Turn on the "Stay awake" switch in Home Assistant to keep the node online for OTA/irrigation.

substitutions:
  name: gardennode
  friendly_name: GardenNode
  sleep_minutes: "10"
  awake_seconds: "25"
  valve_max_minutes: "30"
  # soil probe calibration (volts): measure your probe in dry air and in a glass of water
  soil_dry_v: "2.55"
  soil_wet_v: "1.20"

esphome:
  name: ${name}
  friendly_name: ${friendly_name}
  project:
    name: open-hardware.gardennode-c6
    version: "A.1"
  on_boot:
    priority: 600
    then:
      - output.turn_on: sensor_rail
      - delay: 300ms
      - script.execute: measure

esp32:
  board: esp32-c6-devkitc-1
  variant: esp32c6
  flash_size: 8MB
  framework:
    type: esp-idf

logger:
  hardware_uart: USB_SERIAL_JTAG

api:
  encryption:
    key: !secret api_key
ota:
  - platform: esphome
    password: !secret ota_password

wifi:
  ssid: !secret wifi_ssid
  password: !secret wifi_password
  fast_connect: true
  power_save_mode: light
  ap:
    ssid: "GardenNode Setup"
captive_portal:
improv_serial:

status_led:
  pin:
    number: GPIO11
    inverted: true

deep_sleep:
  id: deep_sleep_ctl
  sleep_duration: ${sleep_minutes}min
  run_duration: ${awake_seconds}s

# ---------- power ----------
output:
  - platform: gpio
    id: sensor_rail          # Q1 P-FET: low = on
    pin: GPIO4
    inverted: true

binary_sensor:
  - platform: gpio
    name: "Charging"
    pin: { number: GPIO18, inverted: true }
    device_class: battery_charging
  - platform: gpio
    name: "External power"
    pin: { number: GPIO19, inverted: true }
    device_class: power

sensor:
  - platform: adc
    id: vbat
    name: "Battery voltage"
    pin: GPIO2
    attenuation: 12db
    samples: 8
    filters: [ multiply: 2.0 ]          # R11/R12 1M:1M
    update_interval: never
    unit_of_measurement: V
    accuracy_decimals: 2
  - platform: template
    name: "Battery"
    unit_of_measurement: "%"
    device_class: battery
    update_interval: never
    id: batt_pct
    lambda: |-
      float v = id(vbat).state;
      float p = (v - 3.30f) / (4.15f - 3.30f) * 100.0f;
      return p < 0 ? 0 : (p > 100 ? 100 : p);
  - platform: adc
    id: vsolar
    name: "Solar voltage"
    pin: GPIO3
    attenuation: 12db
    samples: 4
    filters: [ multiply: 4.0303 ]       # R13/R14 1M:330k
    update_interval: never
    unit_of_measurement: V
    accuracy_decimals: 2
  - platform: adc
    id: soil1_v
    pin: GPIO0
    attenuation: 12db
    samples: 16
    update_interval: never
    internal: true
  - platform: adc
    id: soil2_v
    pin: GPIO1
    attenuation: 12db
    samples: 16
    update_interval: never
    internal: true
  - platform: copy
    source_id: soil1_v
    id: soil1
    name: "Soil moisture 1"
    unit_of_measurement: "%"
    device_class: moisture
    filters:
      - calibrate_linear: [ "${soil_dry_v} -> 0.0", "${soil_wet_v} -> 100.0" ]
      - clamp: { min_value: 0, max_value: 100 }
  - platform: copy
    source_id: soil2_v
    id: soil2
    name: "Soil moisture 2"
    unit_of_measurement: "%"
    device_class: moisture
    filters:
      - calibrate_linear: [ "${soil_dry_v} -> 0.0", "${soil_wet_v} -> 100.0" ]
      - clamp: { min_value: 0, max_value: 100 }
  - platform: dallas_temp
    id: soil_temp
    name: "Soil temperature"
    update_interval: never
  # Qwiic air sensor (Sensirion SHT4x breakout, e.g. Adafruit 4885) - remove if not fitted
  - platform: sht4x
    id: air
    update_interval: never
    temperature: { name: "Air temperature", id: air_t }
    humidity: { name: "Air humidity", id: air_h }
  - platform: wifi_signal
    name: "Wi-Fi signal"
    update_interval: 60s

one_wire:
  - platform: gpio
    pin: GPIO5

i2c:
  sda: GPIO6
  scl: GPIO7
  frequency: 100kHz
  scan: false

# ---------- irrigation valve ----------
switch:
  - platform: gpio
    id: valve
    name: "Valve"
    pin: GPIO10
    icon: mdi:sprinkler-variant
    restore_mode: ALWAYS_OFF
    on_turn_on:
      - deep_sleep.prevent: deep_sleep_ctl
      - delay: ${valve_max_minutes}min      # hard safety limit
      - switch.turn_off: valve
    on_turn_off:
      - if:
          condition: { switch.is_off: stay_awake }
          then: [ deep_sleep.allow: deep_sleep_ctl ]
  - platform: template
    id: stay_awake
    name: "Stay awake"
    optimistic: true
    restore_mode: RESTORE_DEFAULT_OFF
    entity_category: config
    turn_on_action: [ deep_sleep.prevent: deep_sleep_ctl ]
    turn_off_action:
      - if:
          condition: { switch.is_off: valve }
          then: [ deep_sleep.allow: deep_sleep_ctl ]

script:
  - id: measure
    then:
      - component.update: vbat
      - component.update: batt_pct
      - component.update: vsolar
      - component.update: soil1_v
      - component.update: soil2_v
      - component.update: soil_temp
      - component.update: air
      - delay: 1s
      - if:
          condition: { switch.is_off: valve }
          then: [ output.turn_off: sensor_rail ]

button:
  - platform: restart
    name: "Restart"
    entity_category: diagnostic
  - platform: template
    name: "Measure now"
    on_press:
      - output.turn_on: sensor_rail
      - delay: 300ms
      - script.execute: measure
